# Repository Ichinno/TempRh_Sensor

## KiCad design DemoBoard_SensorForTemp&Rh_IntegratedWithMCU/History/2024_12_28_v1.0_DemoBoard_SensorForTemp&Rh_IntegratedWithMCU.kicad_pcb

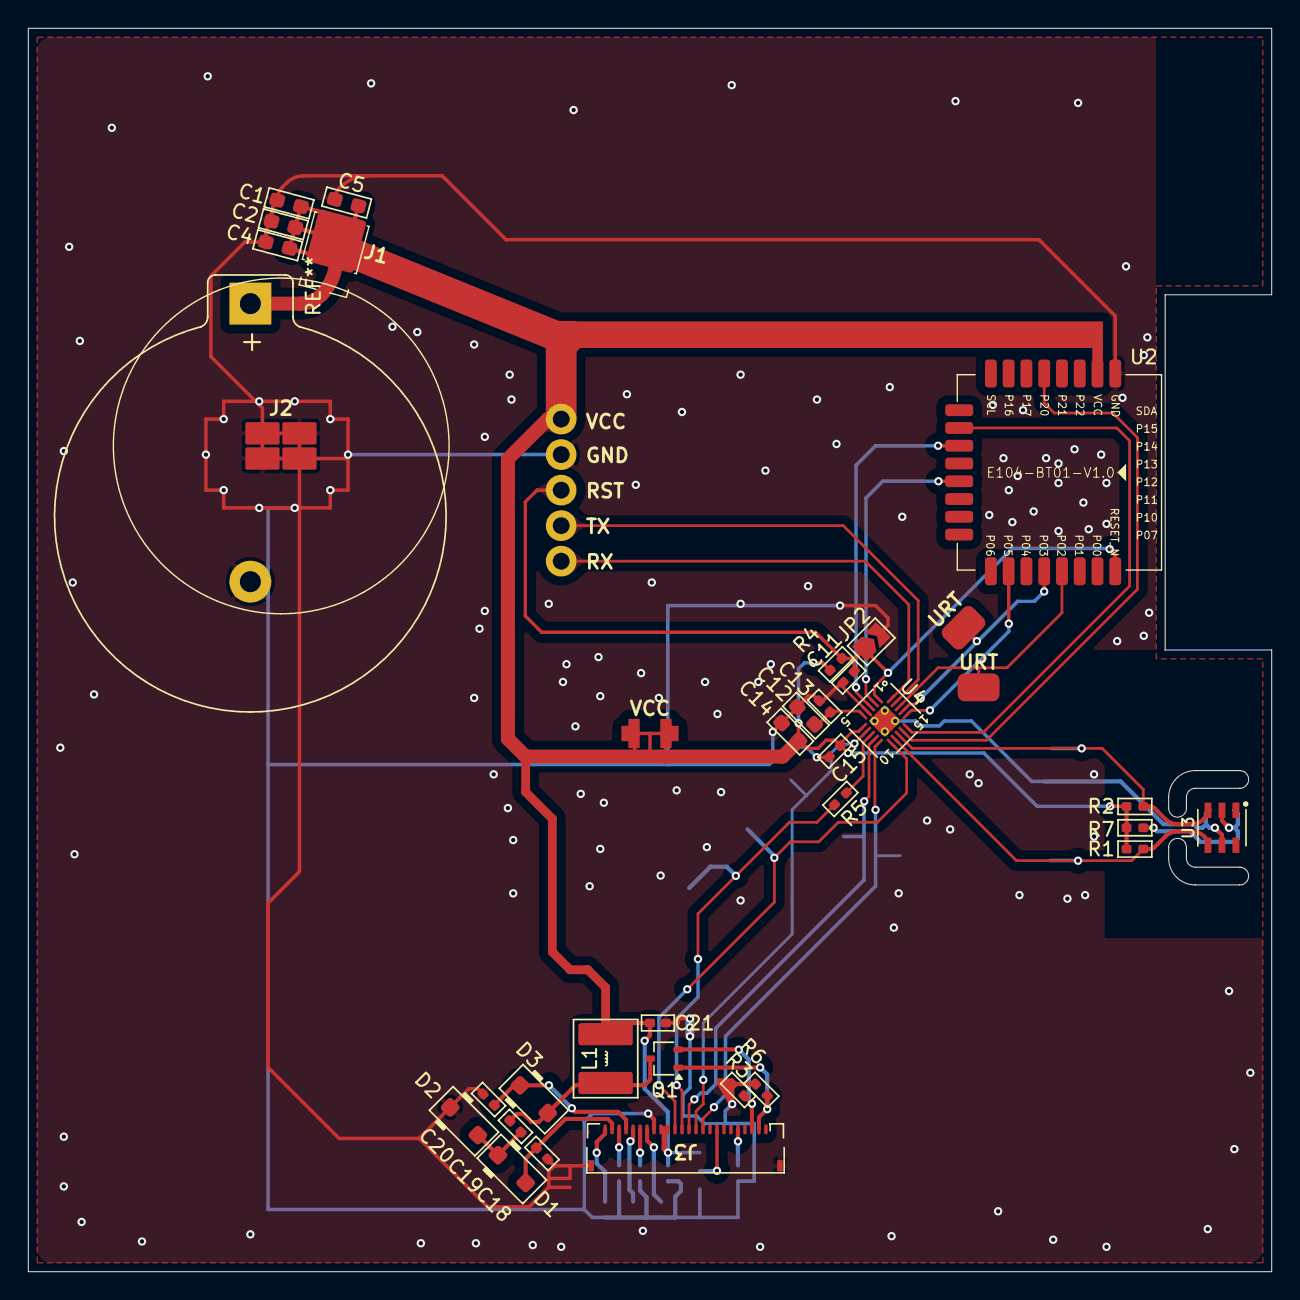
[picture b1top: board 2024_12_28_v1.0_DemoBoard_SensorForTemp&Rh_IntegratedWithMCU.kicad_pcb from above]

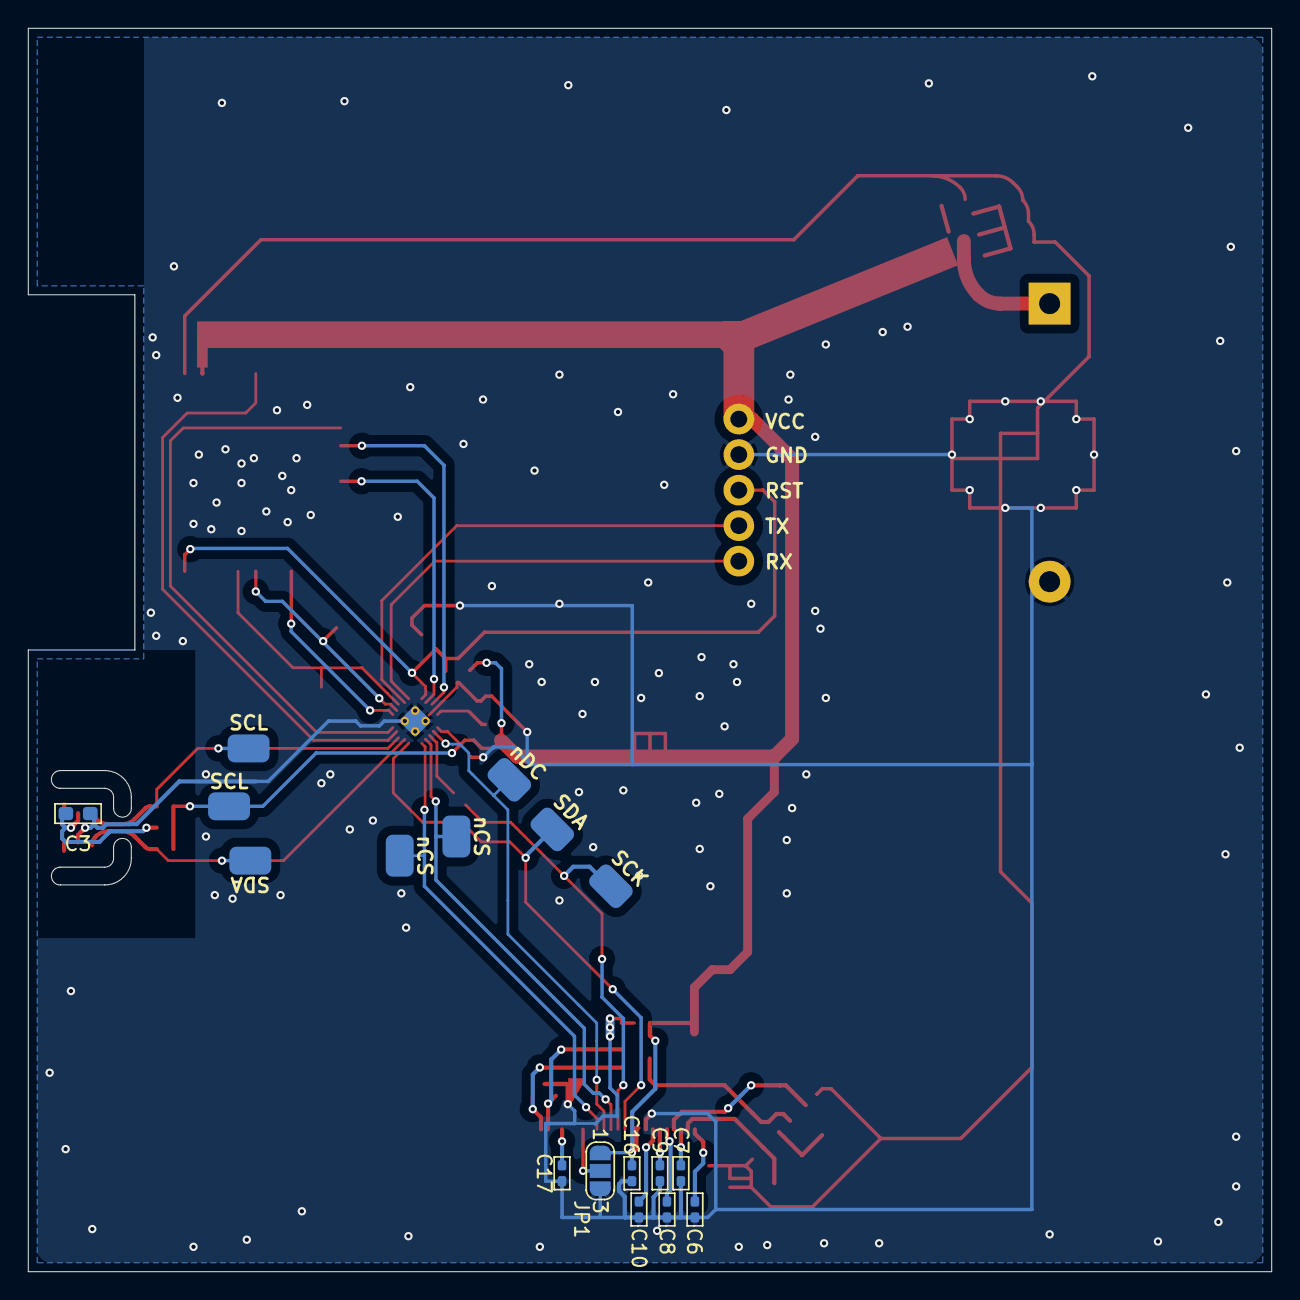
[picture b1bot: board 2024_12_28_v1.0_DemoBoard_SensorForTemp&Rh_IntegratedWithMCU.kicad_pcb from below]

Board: 2 copper layers, 88.9 x 88.9 mm, 57 parts (17 on the bottom side), 34 nets.

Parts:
C1, C2, C4, C5: 22uF; C_0603_1608Metric_Pad1.05x0.95mm_HandSolder
C3: 10u; C_0603_1608Metric_Pad1.05x0.95mm_HandSolder
C6, C9, C10, C16: 1u_6V; C_0402_1005Metric_Pad0.74x0.62mm_HandSolder
C7, C8, C17: 1u_25V; C_0402_1005Metric_Pad0.74x0.62mm_HandSolder
C11, C13, C15: 100n; C_0402_1005Metric_Pad0.74x0.62mm_HandSolder
C12, C14: 4.7u; C_0603_1608Metric_Pad1.05x0.95mm_HandSolder
C18, C19, C20, C21: 1u_50V; C_0402_1005Metric_Pad0.74x0.62mm_HandSolder
D1, D2, D3: MBR0530; D_SOD-123F
J1: Batt_Pos_01x01_Pin; BatteryContactSpring_PODING_BC-1120-X-X
J2: Batt_Neg_01x01_Pin; BatteryContactSpring_PODING_BC-1122-X-X
J3: EPD_OPM015BG_1.54; Hirose_FH34SRJ-24S-0.5SH(50)_1x24_P0.50mm_Horizontal
JP1: Jumper_3_Open; SolderJumper-3_P1.3mm_Open_RoundedPad1.0x1.5mm_NumberLabels
JP2: Jumper; SolderJumper-2_P1.3mm_Open_TrianglePad1.0x1.5mm
L1: 47u; L_Taiyo-Yuden_NR-40xx_BigPads
Q1: SI1304BDL; SOT-323_SC-70
R1, R2: 1k; R_0402_1005Metric_Pad0.72x0.64mm_HandSolder
R3: 2.2; R_0402_1005Metric_Pad0.72x0.64mm_HandSolder
R4: 4.7k; R_0402_1005Metric_Pad0.72x0.64mm_HandSolder
R5: 33; R_0402_1005Metric_Pad0.72x0.64mm_HandSolder
R6: 10k; R_0402_1005Metric_Pad0.72x0.64mm_HandSolder
R7: 330; R_0402_1005Metric_Pad0.72x0.64mm_HandSolder
SCK: TestPad_3x2mm_forTestHook
SCL: TestPad_3x2mm_forTestHook
SCL#2: TestPad_3x2mm_forTestHook
SDA: TestPad_3x2mm_forTestHook
SDA#2: TestPad_3x2mm_forTestHook
TP6, TP7, TP8, TP9, TP10: TestPoint_Alt; TestPoint_D1.2+0.5mm
U2: PE104-BT01
U3: LGA-6_3x3mm_P1.00mm
U4: QFN-20-1EP_3x3mm_P0.4mm_EP1.65x1.65mm_ThermalVias
URT: TestPad_3x2mm_forTestHook
URT#2: TestPad_3x2mm_forTestHook
VCC: TestPad_3x2mm_forTestHook
nCS: TestPad_3x2mm_forTestHook
nCS#2: TestPad_3x2mm_forTestHook
nDC: TestPad_3x2mm_forTestHook

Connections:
/E104-BT01/DATA: U2.11 (P1.4), U4.3 (XTHO/AIN8/P02)
/E104-BT01/DISC: U2.18 (P0.5), U4.16 (P32/AIN2/VCIN2)
/E104-BT01/LINK: U2.10 (P1.5), U4.15 (P31/SWCLK)
/E104-BT01/MOD: U2.5 (P2.0), U4.14 (P27/SWDIO)
/E104-BT01/RST: C11.1, JP2.1 (A), R4.2, TP8.1, U2.24 (RESET_N), U4.1 (RESETB/P00)
/E104-BT01/RX: U2.21 (P0.2), U4.18 (P34/AIN4/VCIN4), URT#2.1
/E104-BT01/TX: U2.20 (P0.3), U4.17 (P33/AIN3/VCIN3), URT.1
/E104-BT01/WKP: U2.13 (P1.2), U4.2 (XTHI/AIN7/VCIN7/P01)
/E-Ink Driver/BS: J3.8, JP1.2 (C)
/E-Ink Driver/GDR: J3.2, Q1.1 (G), R6.2
/E-Ink Driver/PREVGH: C20.1, D3.1 (K), J3.21
/E-Ink Driver/PREVGL: C18.1, D1.2 (A), J3.23
/E-Ink Driver/RESE: J3.3, Q1.2 (S), R3.2
/E-Ink Driver/RST: J3.10, U4.10 (LVDIN2/VCIN0/P23), nCS#2.1
/E-Ink Driver/VCOM: C6.2, J3.24
/E-Ink Driver/VPP: C9.2, J3.19
/E-Ink Driver/VSH: C8.2, J3.20
/E-Ink Driver/VSL: C7.2, J3.22
/E-Ink Driver/nCS: J3.12, U4.9 (XTLI/P14), nCS.1
/E-Ink Driver/nDC: J3.11, U4.7 (LVDIN1/P03), nDC.1
/E-Ink Driver/nSCK: J3.13, R5.1, R5.2, SCK.1, U4.8 (XTLO/P15)
/E-Ink Driver/nSDA: J3.14, SDA.1, U4.11 (P24/AIN0)
/HC32L110_QFN20/UART_RX: TP9.1, U4.20 (P36/AIN6/VCIN6/AVREF)
/HC32L110_QFN20/UART_TX: TP10.1, U4.19 (P35/AIN5/VCIN5)
/HC32L110_QFN20/VCAP: C12.1, C13.1, U4.5 (VCAP)
/SCL: R2.2, SCL.1, U3.3 (SCL), U4.13 (P26/AIN1)
/SDA: R1.2, SDA#2.1, U3.4 (SDA), U4.12 (P25/LVDIN3/VC1)
GND: C1.2, C2.2, C3.2, C4.2, C5.2, C6.1, C7.1, C8.1, C9.1, C10.1, C11.2, C12.2, C13.2, C14.2, C15.2, C16.1, C17.1, C18.2, C20.2, C21.1, D2.1 (K), J2.1, J3.17, J3.MP, JP1.3 (B), JP2.2 (B), R3.1, R6.1, TP7.1, U2.1 (GND), U3.5 (GND), U4.4 (VSS), U4.21 (PAD)
unnamed: C19.2, D1.1 (K), D2.2 (A)
unnamed: C19.1, D3.2 (A), L1.2, Q1.3 (D)
unnamed: C17.2, J3.5
unnamed: C10.2, J3.18
unnamed: C3.1, R7.2, U3.2 (VDD)
VCC: C1.1, C2.1, C4.1, C5.1, C14.1, C15.1, C16.2, C21.2, J1.1, J3.15, J3.16, JP1.1 (A), L1.1, R1.1, R2.1, R4.1, R7.1, SCL#2.1, TP6.1, U2.2 (VCC), U4.6 (VDD), VCC.1

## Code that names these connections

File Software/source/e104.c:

/******************************************************************************
 * Copyright (C) 2021, 
 *
 *  
 *  
 *  
 *  
 *
 ******************************************************************************/
 
/******************************************************************************
 ** @file e104.c
 **
 ** @brief Source file for e104 functions
 **
 ** @author MADS Team 
 **
 ******************************************************************************/

/******************************************************************************
 * Include files
 ******************************************************************************/
#include "gpio.h"
#include "uart_interface.h"

/******************************************************************************
 * Local pre-processor symbols/macros ('#define')                            
 ******************************************************************************/

/******************************************************************************
 * Global variable definitions (declared in header file with 'extern')
 ******************************************************************************/

/******************************************************************************
 * Local type definitions ('typedef')                                         
 ******************************************************************************/

/******************************************************************************
 * Local function prototypes ('static')
 ******************************************************************************/

/******************************************************************************
 * Local variable definitions ('static')                                      *
 ******************************************************************************/

/******************************************************************************
 * Local pre-processor symbols/macros ('#define')                             
 ******************************************************************************/

/*****************************************************************************
 * Function implementation - global ('extern') and local ('static')
 ******************************************************************************/

void E104_ioInit(void)
{
    Gpio_InitIO(3, 1, GpioDirIn);  // Link
    Gpio_InitIOExt(0,1,GpioDirOut,TRUE,FALSE,FALSE,FALSE);   // Wake up
    Gpio_InitIO(0, 2, GpioDirIn);   // Data
    Gpio_InitIOExt(2,7,GpioDirOut,TRUE,FALSE,FALSE,FALSE);   // Mod
    Gpio_InitIOExt(3,2,GpioDirOut,TRUE,FALSE,FALSE,FALSE);   // Disc

    Gpio_SetIO(0,1, FALSE);  // 设置唤醒
    Gpio_SetIO(2,7, TRUE);  // 设置传输模式
    Gpio_SetIO(3,2, TRUE);  // 

}

boolean_t E104_getLinkState(void) // 返回 TRUE 链接成功； FALSE 链接断开
{
    static boolean_t preState = TRUE;
    static boolean_t currentState = TRUE;
    currentState = Gpio_GetIO(3,1);  
    if ((currentState == FALSE) && (preState == TRUE))
    {
        UARTIF_uartPrintf(0, "Link start! \n");
        Gpio_SetIO(3,2, TRUE);  // 
    }
    else if ((currentState == TRUE) && (preState == FALSE))
    {
        UARTIF_uartPrintf(0, "Link end! \n");
    }
    else
    {
        // do nothing
    }
    preState = currentState;
    return !currentState;
}

boolean_t E104_getDataState(void) // 返回 TRUE 数据传输中； FALSE 无数据
{
    static boolean_t preState = TRUE;
    static boolean_t currentState = TRUE;
    currentState = Gpio_GetIO(0,2);  
    if ((currentState == FALSE) && (preState == TRUE))
    {
        UARTIF_uartPrintf(0, "Data on comming! \n");
    }
    else if ((currentState == TRUE) && (preState == FALSE))
    {
        UARTIF_uartPrintf(0, "Data end! \n");
    }
    else
    {
        // do nothing
    }
    preState = currentState;
    return !currentState;
}

void E104_setSleepMode(void)
{
    Gpio_SetIO(0,1, TRUE);
    UARTIF_uartPrintf(0, "Set sleep mode! \n");
}

void E104_setWakeUpMode(void)
{
    Gpio_SetIO(0,1, FALSE);
    UARTIF_uartPrintf(0, "Set wake up mode! \n");

}

void E104_setTransmitMode(void)
{
    Gpio_SetIO(2,7, TRUE);
    UARTIF_uartPrintf(0, "Set transmit mode! \n");

}

void E104_setConfigMode(void)
{
    Gpio_SetIO(2,7, FALSE);
    UARTIF_uartPrintf(0, "Set config mode! \n");

}

void E104_setDisconnect(void)
{
    Gpio_SetIO(3,2, FALSE);
    UARTIF_uartPrintf(0, "Set disconnect! \n");
}

void E104_executeCommand(void)
{
    switch (UARTIF_passThroughCmd())
    {
        case '0':
        E104_setSleepMode();
        break;
        case '1':
        E104_setWakeUpMode();
        break;
        case '2':
        E104_setTransmitMode();
        break;
        case '3':
        E104_setConfigMode();
        break;
        case '4':
        E104_setDisconnect();
        break;
        default:

        break;
    }

}

/******************************************************************************
 * EOF (not truncated)
 ******************************************************************************/

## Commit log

2024-12-24 DemoBoard_SensorForTemp&Rh_IntegratedWithMCU
2025-01-02 Demo_V0.1
2025-01-14 Update Software
2025-02-01 Update for E104
2025-02-03 Update for draw image
2025-02-04 Update for low power mode
